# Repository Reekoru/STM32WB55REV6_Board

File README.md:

# STM32WB55REV6 Custom Development Board

A compact, custom-designed development board for the **STM32WB55REV6** dual-core Bluetooth Low Energy (BLE) and Zigbee microcontroller. Designed in KiCad, this board features a modern USB-C interface for power/data, a dedicated UART interface for debugging, and a space-saving Tag-Connect TC2030 footprint for SWD programming.

## Features

* **MCU:** STM32WB55REV6 (Dual-core Arm® Cortex®-M4 @ 64 MHz with FPU, Cortex-M0+ @ 32 MHz for network/radio).
* **Connectivity:** On-board RF circuitry and antenna for 2.4 GHz BLE 5.4, Zigbee, and Thread.
* **Power:** USB-C connector with TPS78233DDC 3.3V regulator supplying up to 150 mA.
* **Programming/Debugging:** SWD via a headless **Tag-Connect TC2030** footprint (no-legs/legged variant).
* **Serial Communication:** Dedicated UART breakout header for easy terminal debugging.
* **Peripherals:** 
    * 1x User LED (connected to Pin `PB9`)
    * USB-UART (connected to Pin `PA9` [TX], Pin `PA10` [RX])
    * 1x Reset Button, 1x Boot Button
    * External 32.768 kHz LSE Crystal, 32 MHz HSE Crystal

---

## Hardware Overview

### Pinout Configuration

| Interface | Pin Name | STM32WB55 Pin | Description |
| :--- | :--- | :--- | :--- |
| **UART** | TX / RX | PA9 / PA10 | Debug Serial Port |
| **SWD** | SWO / SWDIO / SWCLK | PB3 / PA13 / PA14 | Tag-Connect TC2030 Programming |
| **User LED** | LED1 | PB9 | Active [High/Low] indicator |

### Power Supply
The board is powered via the **USB-C** connector. The input 5V is regulated down to 3.3V for the MCU and RF front end. 
* **Maximum input voltage:** 5.5V
* **Operating voltage:** 3.3V

---

## Programming and Debugging

### Required Hardware
To flash and debug this board, you will need:
1.  An ST-LINK V2, V3, or a Segger J-Link debugger.
2.  A **Tag-Connect TC2030-IDC** (or TC2030-IDC-NL) cable along with the corresponding retaining clip if using the no-legs version.

### SWD Pinout (TC2030 Footprint)
The Tag-Connect footprint maps to the following standard SWD layout:
* Pin 1: VCC (3.3V)
* Pin 2: SWDIO
* Pin 3: NRST (Reset)
* Pin 4: SWCLK
* Pin 5: GND
* Pin 6: SWO (Optional trace capture)

### Flashing via STM32CubeProgrammer
1. Connect the TC2030 cable to the board and your ST-LINK debugger.
2. Open **STM32CubeProgrammer**, select **ST-LINK** as the interface, and click **Connect**.
3. Browse for your compiled binary/hex file and click **Start Programming**.

---

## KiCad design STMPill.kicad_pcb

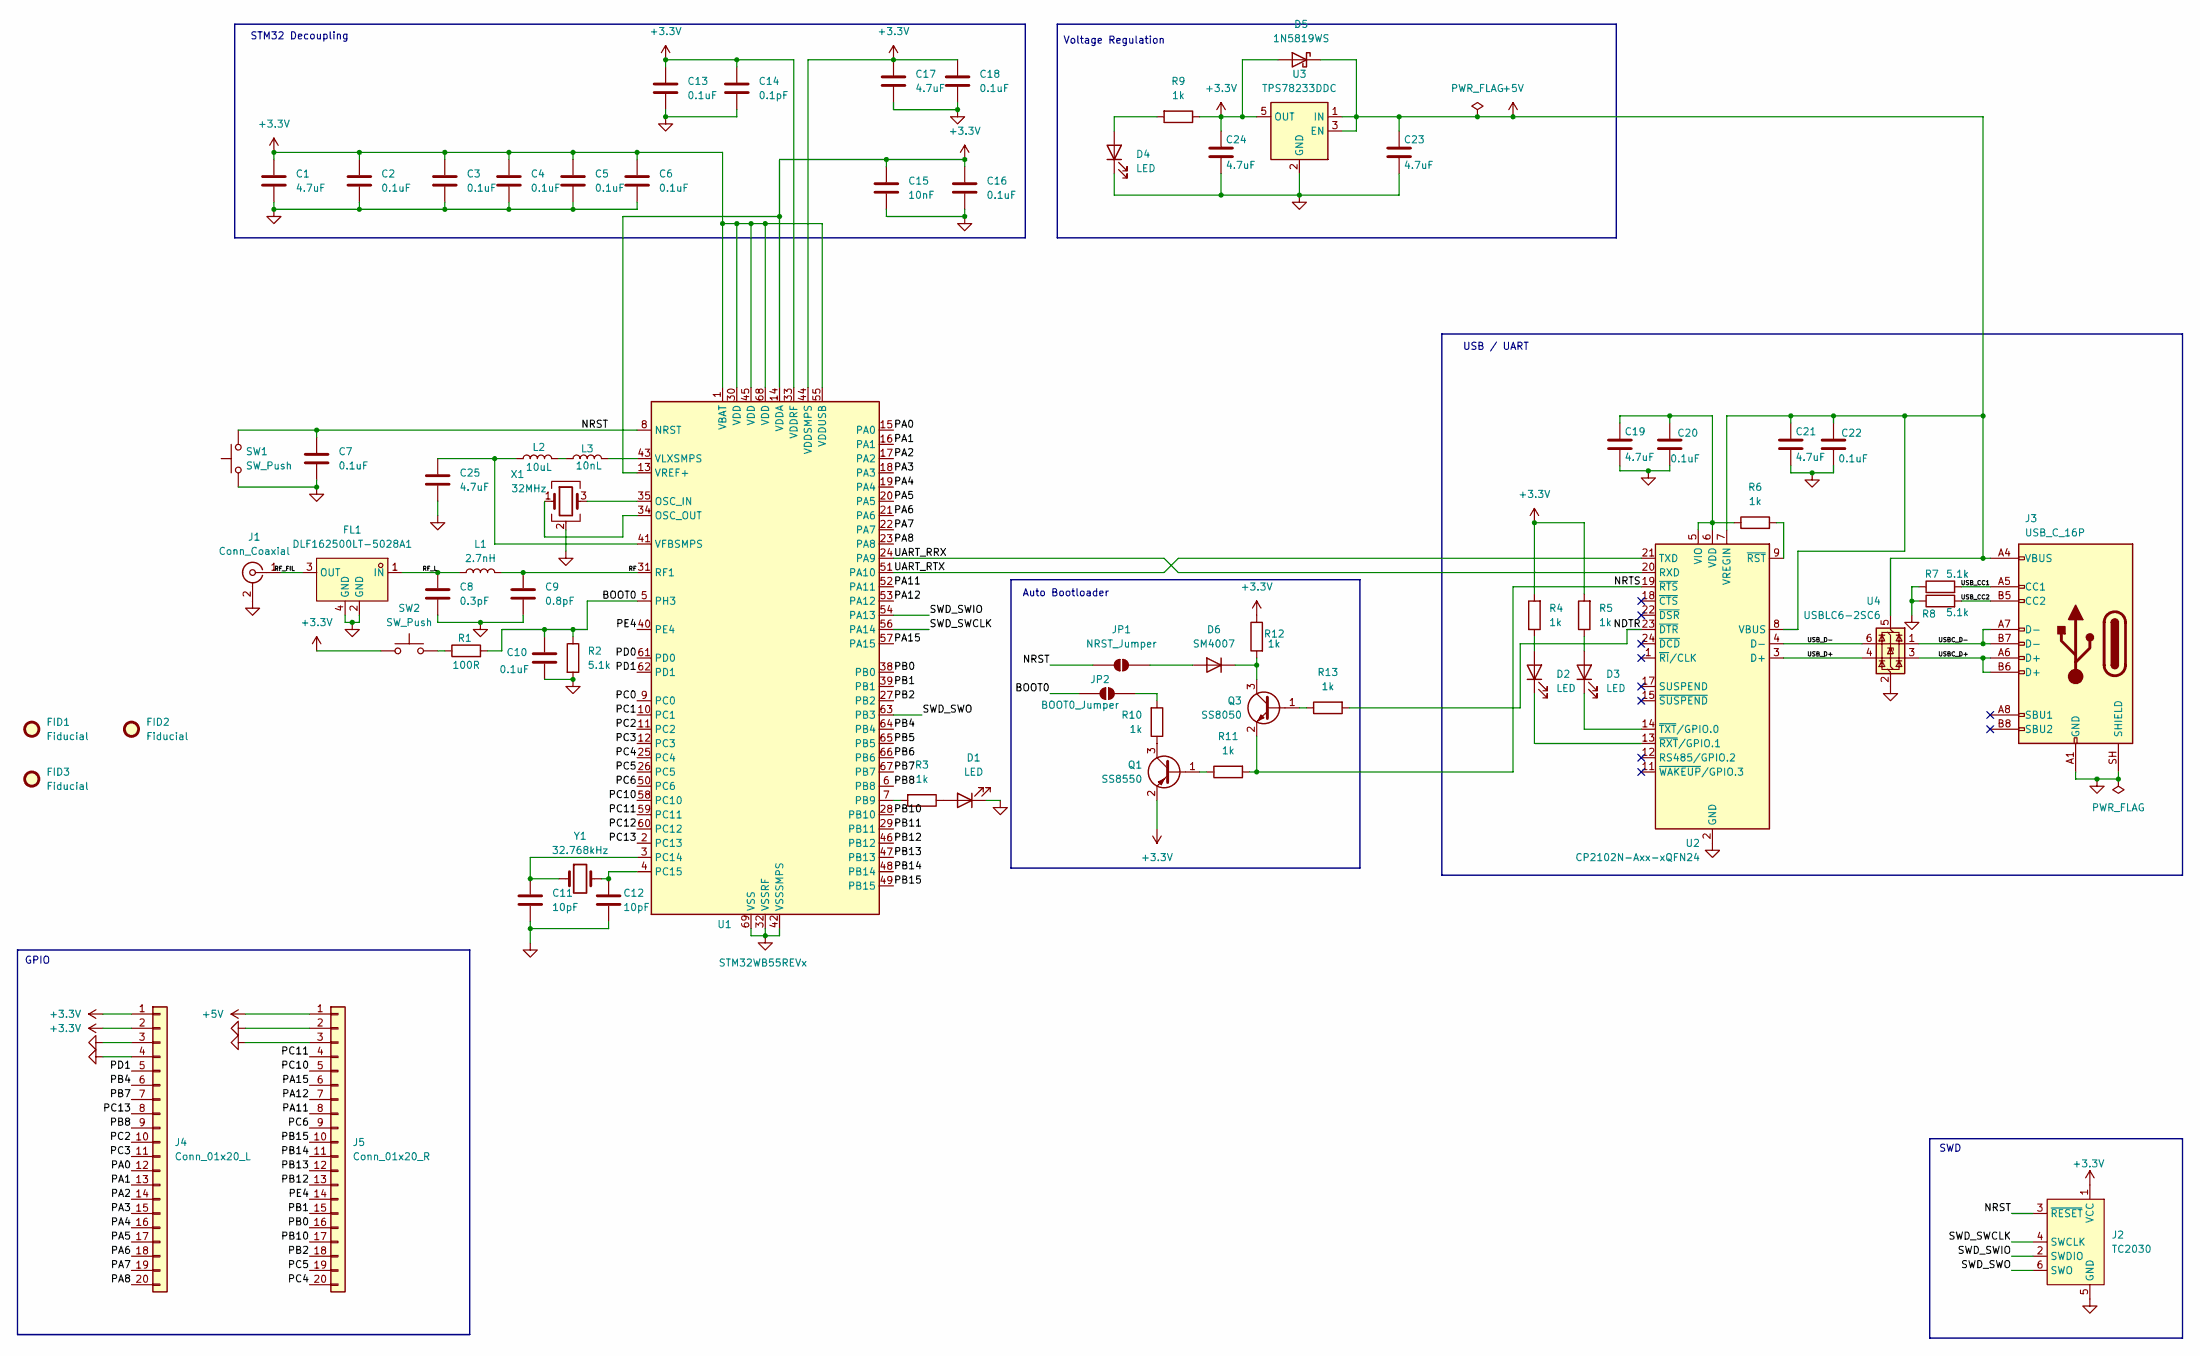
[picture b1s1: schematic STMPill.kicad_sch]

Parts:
C1, C17, C19, C21, C23, C24, C25: 4.7uF; C_0402_1005Metric; LCSC Part C23733
C2, C3, C4, C5, C6, C7, C10, C13, C16, C18, C20, C22: 0.1uF; C_0402_1005Metric; LCSC Part C1525
C8: 0.3pF; C_0402_1005Metric; LCSC Part C92338
C9: 0.8pF; C_0402_1005Metric; LCSC Part C76988
C11, C12: 10pF; C_0402_1005Metric; LCSC Part C1845716
C14: 0.1pF; C_0402_1005Metric; LCSC Part C53273
C15: 10nF; C_0402_1005Metric; LCSC Part C1525
D1, D3, D4: LED; D_0402_1005Metric; LCSC Part C598352
D2: LED; D_0402_1005Metric; LCSC Part C130720
D5: 1N5819WS; D_SOD-323; LCSC Part C191023
D6: SM4007; D_SOD-123F; LCSC Part C64898
FID1, FID2, FID3: Fiducial; Fiducial_0.5mm_Mask1mm
FL1: DLF162500LT-5028A1; FILTER-SMD_0603-4P-L1.6-W0.8-L-1; MPN DLF162500LT-5028A1; LCSC Part C531364
J1: Conn_Coaxial; U.FL_Hirose_U.FL-R-SMT-1_Vertical; LCSC Part C88374
J2: TC2030; Tag-Connect_TC2030-IDC-FP_2x03_P1.27mm_Vertical
J3: USB_C_16P; USB_C_Receptacle_GCT_USB4105-xx-A_16P_TopMnt_Horizontal; LCSC Part C165948
J4: Conn_01x20_L; PinSocket_1x20_P2.54mm_Vertical
J5: Conn_01x20_R; PinSocket_1x20_P2.54mm_Vertical
JP1: NRST_Jumper; SolderJumper-2_P1.3mm_Open_RoundedPad1.0x1.5mm
JP2: BOOT0_Jumper; SolderJumper-2_P1.3mm_Open_RoundedPad1.0x1.5mm
L1: 2.7nH; L_0402_1005Metric; LCSC Part C77108
L2: 10uL; L_0805_2012Metric; LCSC Part C162582
L3: 10nL; L_0402_1005Metric; LCSC Part C3911026
Q1: SS8550; SOT-23; LCSC Part C8542
Q3: SS8050; SOT-23; LCSC Part C2150
R1: 100R; R_0402_1005Metric; LCSC Part C25076
R2, R7, R8: 5.1k; R_0402_1005Metric; LCSC Part C25905
R3, R4, R5, R6, R9, R10, R11, R12, R13: 1k; R_0402_1005Metric; LCSC Part C11702
SW1, SW2: SW_Push; KEY-SMD_L3.9-W3.0-LS5.0-EH; LCSC Part C18078117
U1: STM32WB55REVx; QFN-68-1EP_8x8mm_P0.4mm_EP6.4x6.4mm; LCSC Part C1558409
U2: CP2102N-Axx-xQFN24; QFN-24-1EP_4x4mm_P0.5mm_EP2.6x2.6mm; LCSC Part C969151
U3: TPS78233DDC; SOT-23-5; LCSC Part C14878
U4: USBLC6-2SC6; SOT-23-6; LCSC Part C7519
X1: 32MHz; Crystal_SMD_2016-4Pin_2.0x1.6mm; LCSC Part C843260
Y1: 32.768kHz; SMD3215-2P; LCSC Part C7294751

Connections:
+3.3V: C1.1, C2.1, C3.1, C4.1, C5.1, C6.1, C13.1, C14.1, C15.1, C16.1, C17.1, C18.1, C24.1, D5.2 (A), J2.1 (VCC), J4.1, J4.2, Q1.2 (E), R4.2, R5.2, R9.1, R12.1, SW2.1, U1.1 (VBAT), U1.13 (VREF+), U1.14 (VDDA), U1.30 (VDD), U1.33 (VDDRF), U1.44 (VDDSMPS), U1.45 (VDD), U1.55 (VDDUSB), U1.68 (VDD), U3.5 (OUT)
+5V: C21.1, C22.1, C23.1, D5.1 (K), J3.A4 (VBUS), J3.A9 (VBUS), J3.B4 (VBUS), J3.B9 (VBUS), J5.1, U2.7 (VREGIN), U2.8 (VBUS), U3.1 (IN), U3.3 (EN), U4.5 (VBUS)
/BOOT0: C10.1, JP2.1 (A), R1.2, R2.1, U1.5 (PH3)
/NDTR: R13.2, U2.23 (~DTR)
/NRST: C7.1, J2.3 (~RESET), JP1.1 (A), SW1.2, U1.8 (NRST)
/NRTS: Q3.2 (E), R11.2, U2.19 (~RTS)
/PA0: J4.12, U1.15 (PA0)
/PA1: J4.13, U1.16 (PA1)
/PA2: J4.14, U1.17 (PA2)
/PA3: J4.15, U1.18 (PA3)
/PA4: J4.16, U1.19 (PA4)
/PA5: J4.17, U1.20 (PA5)
/PA6: J4.18, U1.21 (PA6)
/PA7: J4.19, U1.22 (PA7)
/PA8: J4.20, U1.23 (PA8)
/PA11: J5.8, U1.52 (PA11)
/PA12: J5.7, U1.53 (PA12)
/PA15: J5.6, U1.57 (PA15)
/PB0: J5.16, U1.38 (PB0)
/PB1: J5.15, U1.39 (PB1)
/PB2: J5.18, U1.27 (PB2)
/PB4: J4.6, U1.64 (PB4)
/PB5: U1.65 (PB5)
/PB6: U1.66 (PB6)
/PB7: J4.7, U1.67 (PB7)
/PB8: J4.9, U1.6 (PB8)
/PB10: J5.17, U1.28 (PB10)
/PB11: U1.29 (PB11)
/PB12: J5.13, U1.46 (PB12)
/PB13: J5.12, U1.47 (PB13)
/PB14: J5.11, U1.48 (PB14)
/PB15: J5.10, U1.49 (PB15)
/PC0: U1.9 (PC0)
/PC1: U1.10 (PC1)
/PC2: J4.10, U1.11 (PC2)
/PC3: J4.11, U1.12 (PC3)
/PC4: J5.20, U1.25 (PC4)
/PC5: J5.19, U1.26 (PC5)
/PC6: J5.9, U1.50 (PC6)
/PC10: J5.5, U1.58 (PC10)
/PC11: J5.4, U1.59 (PC11)
/PC12: U1.60 (PC12)
/PC13: J4.8, U1.2 (PC13)
/PD0: U1.61 (PD0)
/PD1: J4.5, U1.62 (PD1)
/PE4: J5.14, U1.40 (PE4)
/RF: C9.1, L1.2, U1.31 (RF1)
/RF_FIL: FL1.3 (OUT), J1.1 (In)
/RF_L: C8.1, FL1.1 (IN), L1.1
/SWD_SWCLK: J2.4 (SWCLK), U1.56 (PA14)
/SWD_SWIO: J2.2 (SWDIO), U1.54 (PA13)
/SWD_SWO: J2.6 (SWO), U1.63 (PB3)
/UART_RRX: U1.24 (PA9), U2.20 (RXD)
/UART_RTX: U1.51 (PA10), U2.21 (TXD)
/USBC_D+: J3.A6 (D+), J3.B6 (D+), U4.3 (I/O2)
/USBC_D-: J3.A7 (D-), J3.B7 (D-), U4.1 (I/O1)
/USB_CC1: J3.A5 (CC1), R7.2
/USB_CC2: J3.B5 (CC2), R8.2
/USB_D+: U2.3 (D+), U4.4 (I/O2)
/USB_D-: U2.4 (D-), U4.6 (I/O1)
GND: C1.2, C2.2, C3.2, C4.2, C5.2, C6.2, C7.2, C8.2, C9.2, C10.2, C11.2, C12.2, C13.2, C14.2, C15.2, C16.2, C17.2, C18.2, C19.2, C20.2, C21.2, C22.2, C23.2, C24.2, C25.2, D1.1 (K), D4.1 (K), FL1.2 (GND), FL1.4 (GND), J1.2 (Ext), J2.5 (GND), J3.A1 (GND), J3.A12 (GND), J3.B1 (GND), J3.B12 (GND), J3.SH (SHIELD), J4.3, J4.4, J5.2, J5.3, R2.2, R7.1, R8.1, SW1.1, U1.32 (VSSRF), U1.42 (VSSSMPS), U1.69 (VSS), U2.2 (GND), U2.25 (GND), U3.2 (GND), U3.4 (GND), U4.2 (GND), X1.2 (G), X1.4 (G)
unnamed: D1.2 (A), R3.1
unnamed: D2.2 (A), R4.1
unnamed: D2.1 (K), U2.13 (~RXT/GPIO.1)
unnamed: D3.2 (A), R5.1
unnamed: D3.1 (K), U2.14 (~TXT/GPIO.0)
unnamed: D4.2 (A), R9.2
unnamed: D6.2 (A), JP1.2 (B)
unnamed: D6.1 (K), Q3.3 (C), R12.2
unnamed: JP2.2 (B), R10.2
unnamed: L2.2, L3.1
unnamed: Q1.1 (B), R11.1
unnamed: Q1.3 (C), R10.1
unnamed: Q3.1 (B), R13.1
unnamed: R1.1, SW2.2
unnamed: U1.35 (OSC_IN), X1.3
unnamed: U1.34 (OSC_OUT), X1.1
unnamed: R3.2, U1.7 (PB9)
unnamed: C11.1, U1.3 (PC14), Y1.1
unnamed: C12.1, U1.4 (PC15), Y1.2
unnamed: C25.1, L2.1, U1.41 (VFBSMPS)
unnamed: L3.2, U1.43 (VLXSMPS)
unnamed: C19.1, C20.1, R6.1, U2.5 (VIO), U2.6 (VDD)
unnamed: R6.2, U2.9 (~RST)

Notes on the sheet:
Auto Bootloader
STM32 Decoupling
GPIO
USB / UART
Voltage Regulation
SWD

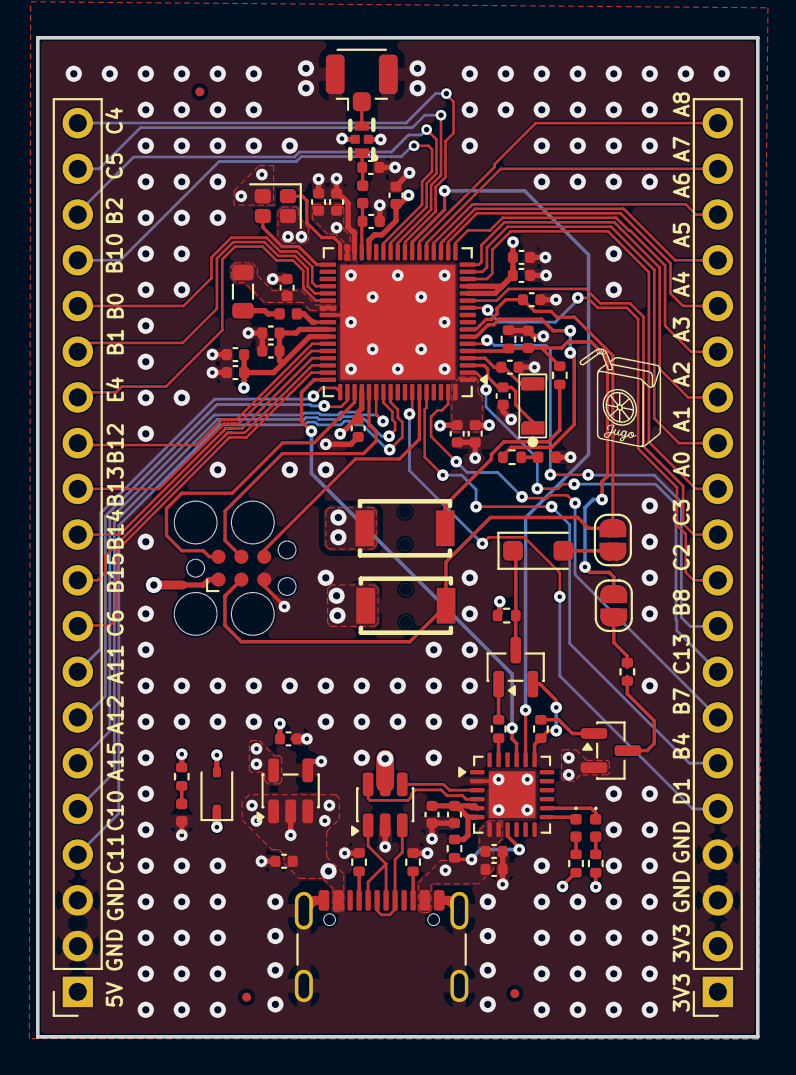
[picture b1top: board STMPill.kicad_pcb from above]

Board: 4 copper layers, 40.0 x 55.5 mm, 68 parts (0 on the bottom side), 77 nets.

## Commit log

2026-06-06 saving
2026-06-07 touchups
2026-06-07 edit gitignore
2026-06-12 fixing footprints
2026-06-12 readme
